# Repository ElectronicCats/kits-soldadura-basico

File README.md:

# Kits de soldadura básico · Electronic Cats

Cuatro gatos para aprender a soldar componentes de inserción (through hole): **Gatito Esotérico**, **Robocat**,
**Mariachi Meow** y **Gato Alebrije**. Al terminar y poner la pila, los ojos del gato parpadean alternados.

Se regalaron 100 kits en la Villa del Hardware de BugCON 2026 (CDMX), con el patrocinio de UNIT Electronics.

**Guía en video paso a paso:** https://youtu.be/u02vvQnGIQA

## Qué trae cada kit

| Cant. | Pieza | Referencia en la placa |
|---|---|---|
| 1 | PCB del gato | — |
| 2 | LED amarillo 3 mm | D1, D2 |
| 2 | Capacitor electrolítico 100 µF / 16 V | C3, C4 |
| 2 | Resistencia axial 330 Ω | R1, R4 |
| 2 | Resistencia axial 1 kΩ | R2, R3 |
| 2 | Transistor NPN BC547 | Q1, Q2 (en el Robocat: Q3, Q4) |
| 1 | Portapilas CR2032 | BT1 (va por detrás) |
| 1 | Switch SMD | SW2 (va por detrás) |

La pila CR2032 no viene en la lista de materiales del kit.

## Cómo se arma

1. **LED** (D1, D2). Tienen polaridad: la pata larga va en **+**.
2. **Capacitores** (C3, C4). Tienen polaridad: la franja va en **−**. Corta las patitas que sobran.
3. **Resistencias**: 330 Ω en R1 y R4, 1 kΩ en R2 y R3. No tienen polaridad.
4. **Transistores** (Q1, Q2). La cara plana va como en el dibujo de la placa.
5. **La vuelta**: portapilas.
6. **La vuelta**: switch. Fíjalo con pinzas y suelda una patita primero.
7. Pon la pila CR2032 con el **+** hacia afuera y mueve el switch a **ON**.

## Cómo funciona

Es un oscilador de dos transistores (multivibrador astable). Cada LED va **en paralelo** con su transistor, del
colector a tierra, y se alimenta por su resistencia de 330 Ω: cuando el transistor conduce, apaga su LED; cuando se
corta, el LED enciende. Los capacitores cruzan cada colector con la base del otro transistor y las resistencias de
1 kΩ cargan las bases, así que los dos LED se alternan unas seis veces por segundo.

**Por qué 1 kΩ y 100 µF (y no 100 kΩ y 10 µF):** para apagar su LED, cada transistor debe hundir unos 9 mA
(3.3 V / 330 Ω). Con 100 kΩ en la base sólo le entran ~26 µA y un BC547 no se satura: el colector apenas baja,
el LED amarillo fija el nivel alto en ~2 V y el salto que pasa al otro transistor (~0.4 V) no alcanza para cortarlo.
Los dos se quedan a medias y el circuito no oscila. Con 1 kΩ la base recibe ~2.6 mA, el transistor se satura y
conmuta limpio; el capacitor sube a 100 µF para que el parpadeo no sea demasiado rápido.

## Hardware

Diseñado en KiCad 9. Cada gato tiene su proyecto en `hardware/Kit_<gato>/` (esquemático, PCB y vistas frontal y
trasera en SVG). Los archivos de fabricación se generan con KiBot (`.github/workflows/kicad_fabrication_files.yml`).

Diseño: Electronic Cats.

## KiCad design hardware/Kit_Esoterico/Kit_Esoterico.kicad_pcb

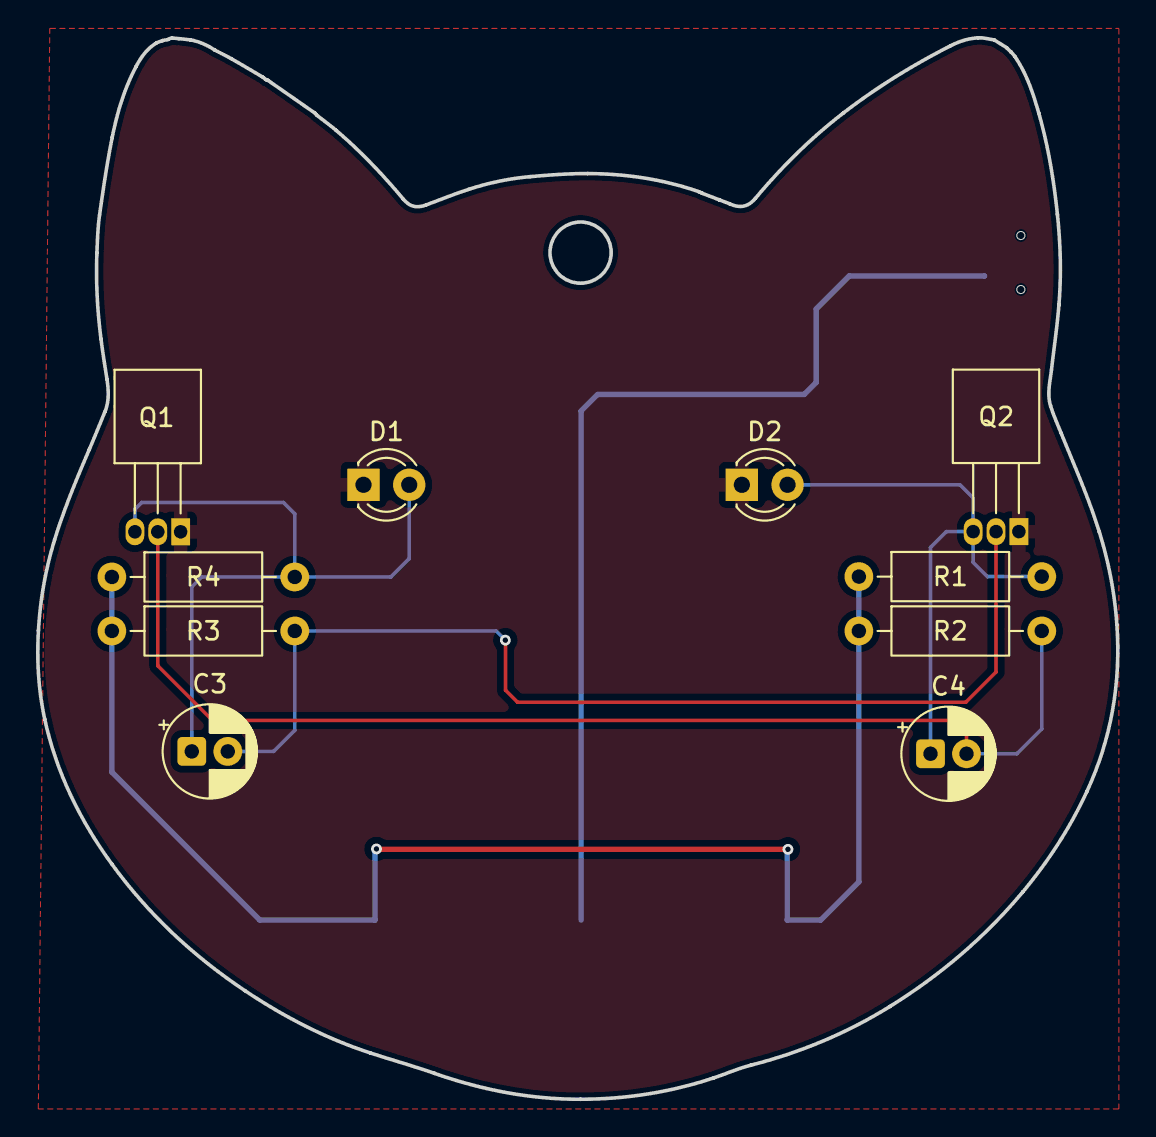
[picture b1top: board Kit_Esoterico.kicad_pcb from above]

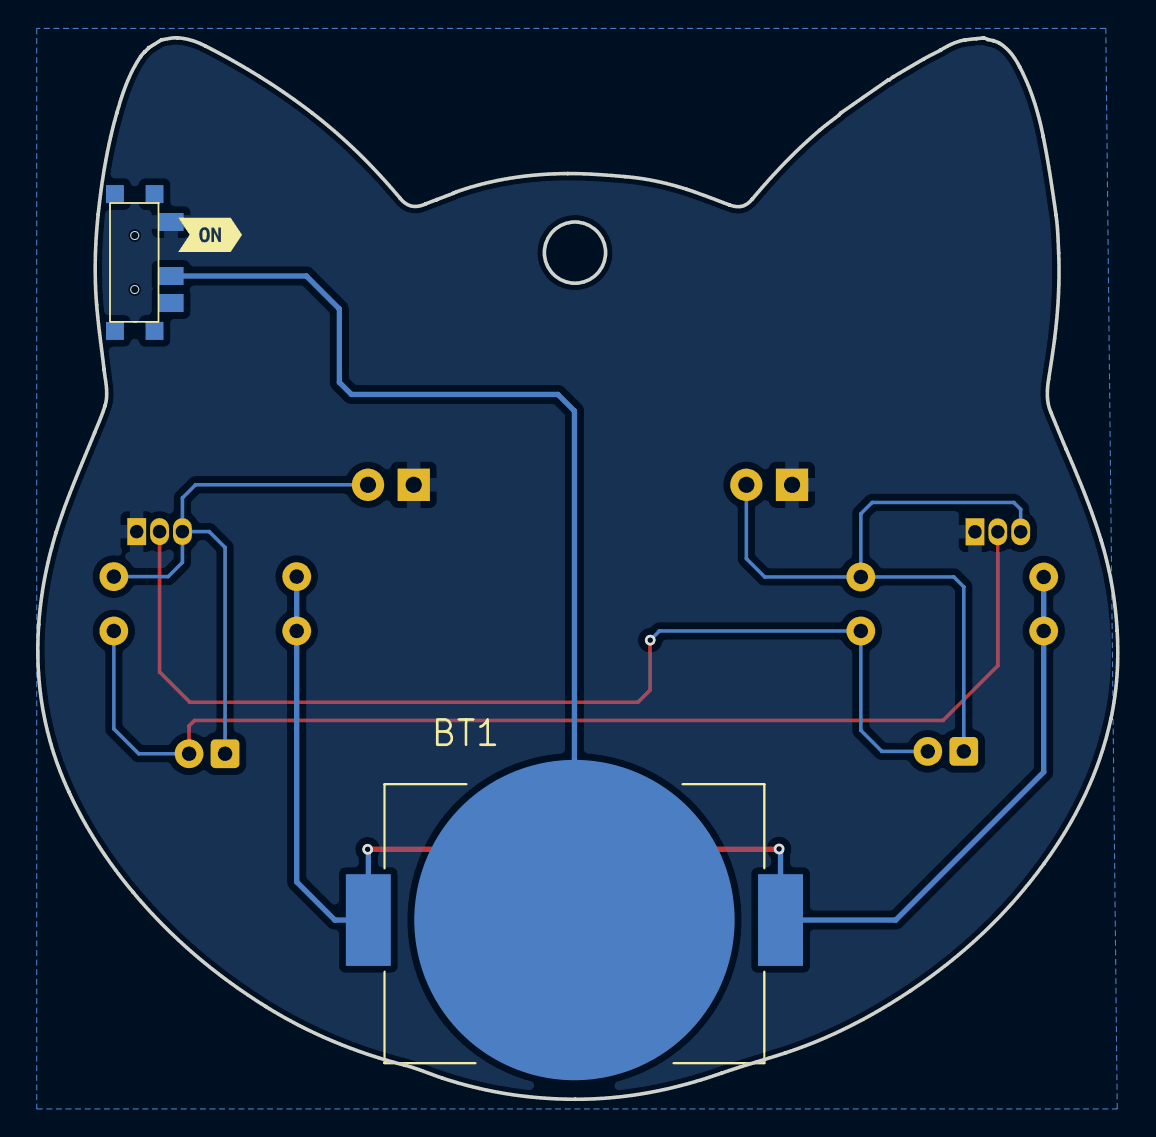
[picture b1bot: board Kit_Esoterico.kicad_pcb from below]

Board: 2 copper layers, 60.0 x 59.0 mm, 13 parts (3 on the bottom side), 7 nets.

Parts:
BT1: Battery_Cell; BAT_BAT-HLD-001
C3, C4: 100uF; CP_Radial_D5.0mm_P2.00mm
D1, D2: YELLOW; LED_D3.0mm
Q1, Q2: BC547; TO-92_Inline_Horizontal1
R1, R4: 330R; R_Axial_DIN0207_L6.3mm_D2.5mm_P10.16mm_Horizontal
R2, R3: 1K; R_Axial_DIN0207_L6.3mm_D2.5mm_P10.16mm_Horizontal
SW2: On; SW-SMD_3P-P1.50_L2.7-W6.6
kibuzzard-6AC56228: G***; kibuzzard-6AC56228

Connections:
+3.3V: BT1.2 (+), R1.1, R2.1, R3.1, R4.1
GND: D1.1 (K), D2.1 (K), Q1.1 (E), Q2.1 (E), SW2.1 (A)
unnamed: BT1.1 (-), SW2.2 (B)
unnamed: C3.1, D1.2 (A), Q1.3 (C), R4.2
unnamed: C4.1, D2.2 (A), Q2.3 (C), R1.2
unnamed: C4.2, Q1.2 (B), R2.2
unnamed: C3.2, Q2.2 (B), R3.2

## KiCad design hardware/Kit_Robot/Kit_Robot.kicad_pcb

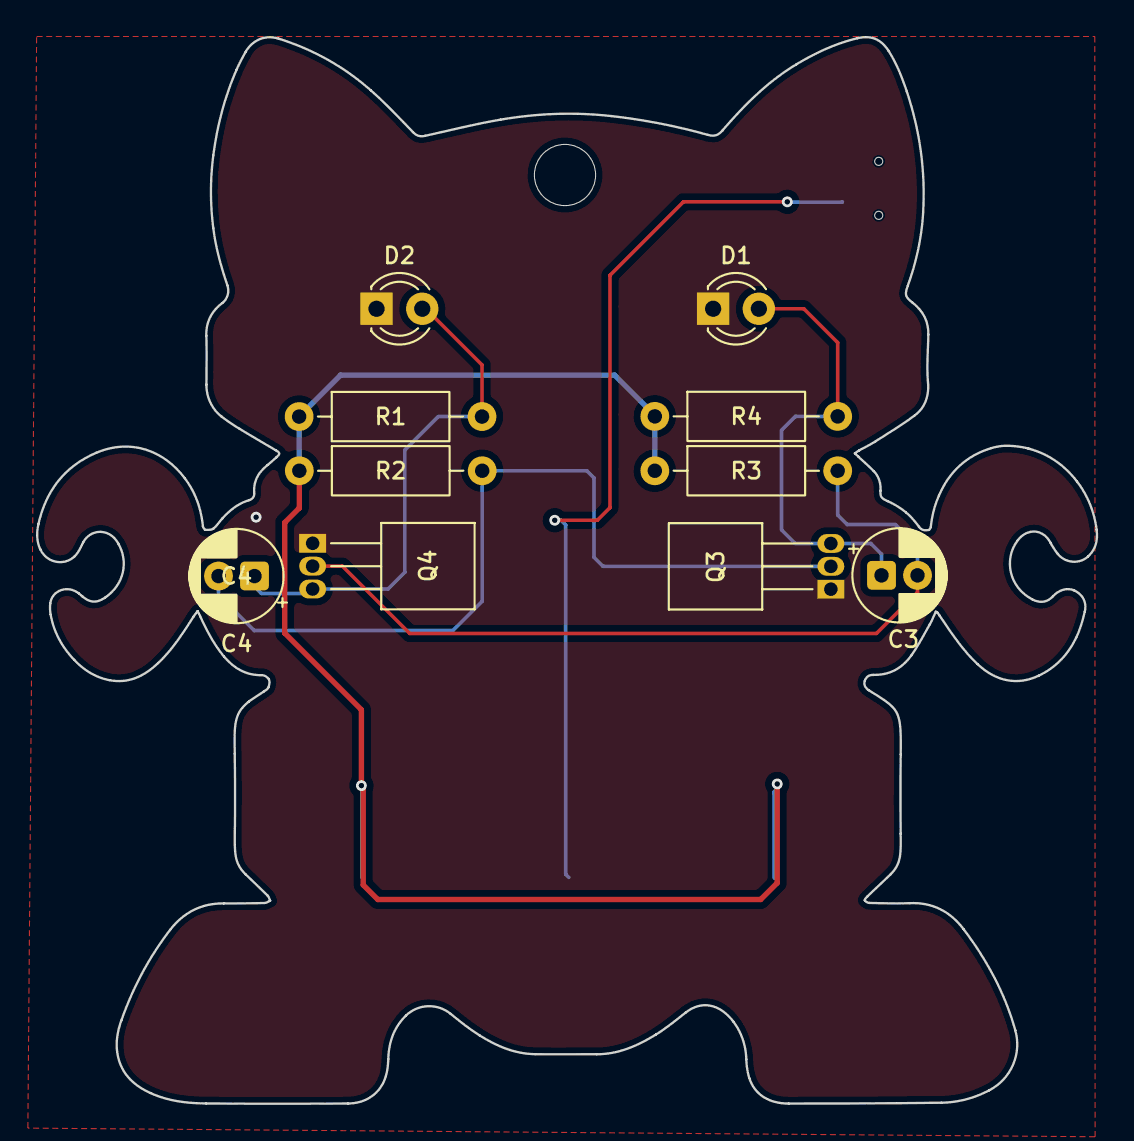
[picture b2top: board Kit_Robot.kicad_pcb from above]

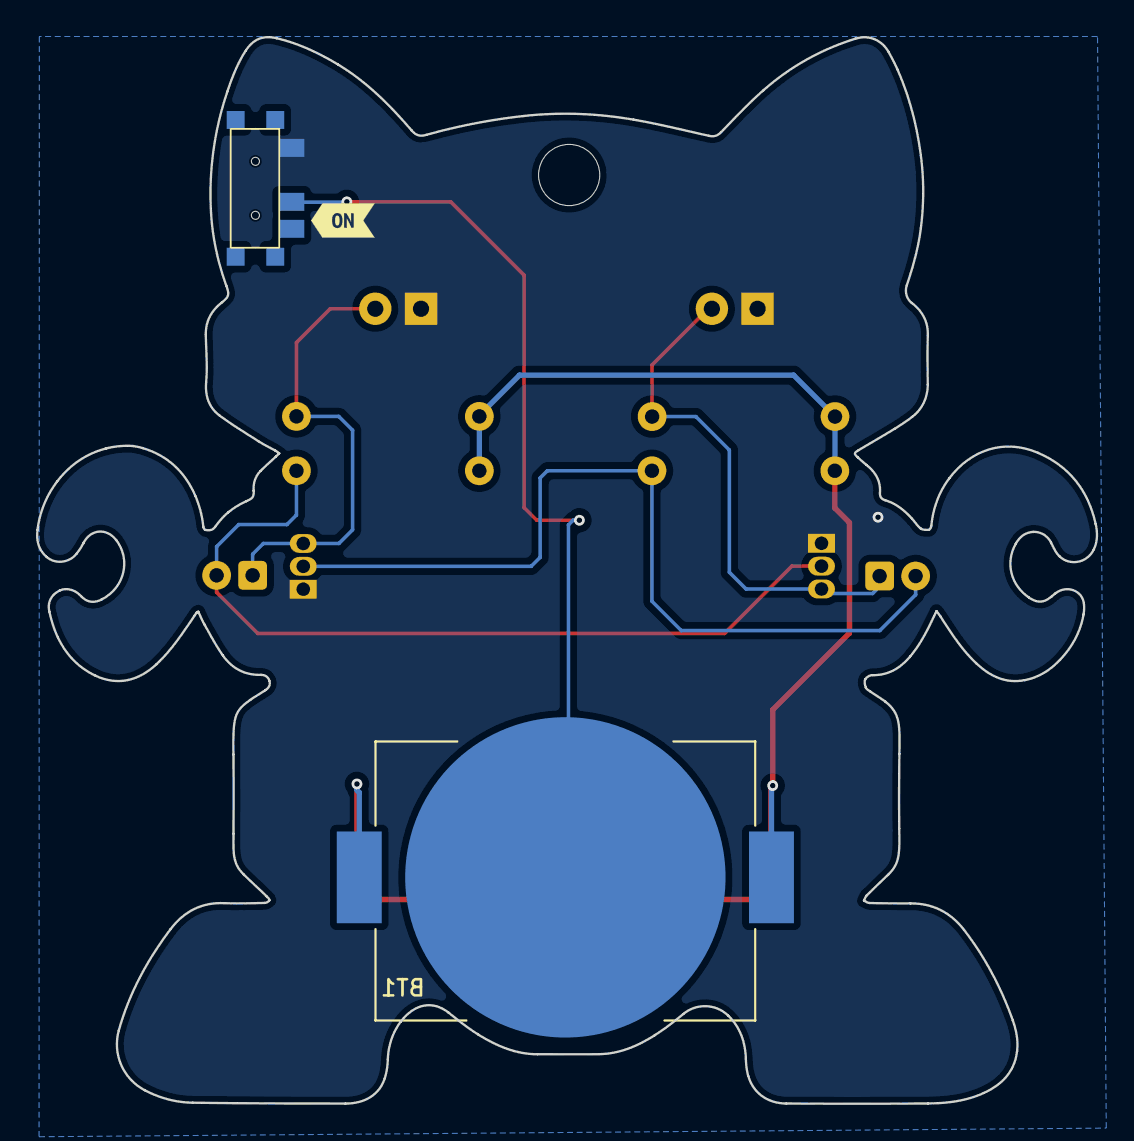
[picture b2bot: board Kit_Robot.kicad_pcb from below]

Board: 2 copper layers, 58.9 x 59.3 mm, 13 parts (3 on the bottom side), 7 nets.

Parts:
BT1: Battery_Cell; BAT_BAT-HLD-001
C3, C4: 100uF; CP_Radial_D5.0mm_P2.00mm
D1, D2: YELLOW; LED_D3.0mm
Q3, Q4: BC547; TO-92_Inline_Horizontal2
R1, R4: 330R; R_Axial_DIN0207_L6.3mm_D2.5mm_P10.16mm_Horizontal
R2, R3: 1K; R_Axial_DIN0207_L6.3mm_D2.5mm_P10.16mm_Horizontal
SW2: On; SW-SMD_3P-P1.50_L2.7-W6.6
kibuzzard-6AC42980: G***; kibuzzard-6AC42980

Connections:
+3.3V: BT1.2 (+), R1.1, R2.1, R3.1, R4.1
GND: D1.1 (K), D2.1 (K), Q3.1 (E), Q4.1 (E), SW2.1 (A)
unnamed: BT1.1 (-), SW2.2 (B)
unnamed: C3.1, D1.2 (A), Q3.3 (C), R4.2
unnamed: C4.1, D2.2 (A), Q4.3 (C), R1.2
unnamed: C4.2, Q3.2 (B), R2.2
unnamed: C3.2, Q4.2 (B), R3.2
